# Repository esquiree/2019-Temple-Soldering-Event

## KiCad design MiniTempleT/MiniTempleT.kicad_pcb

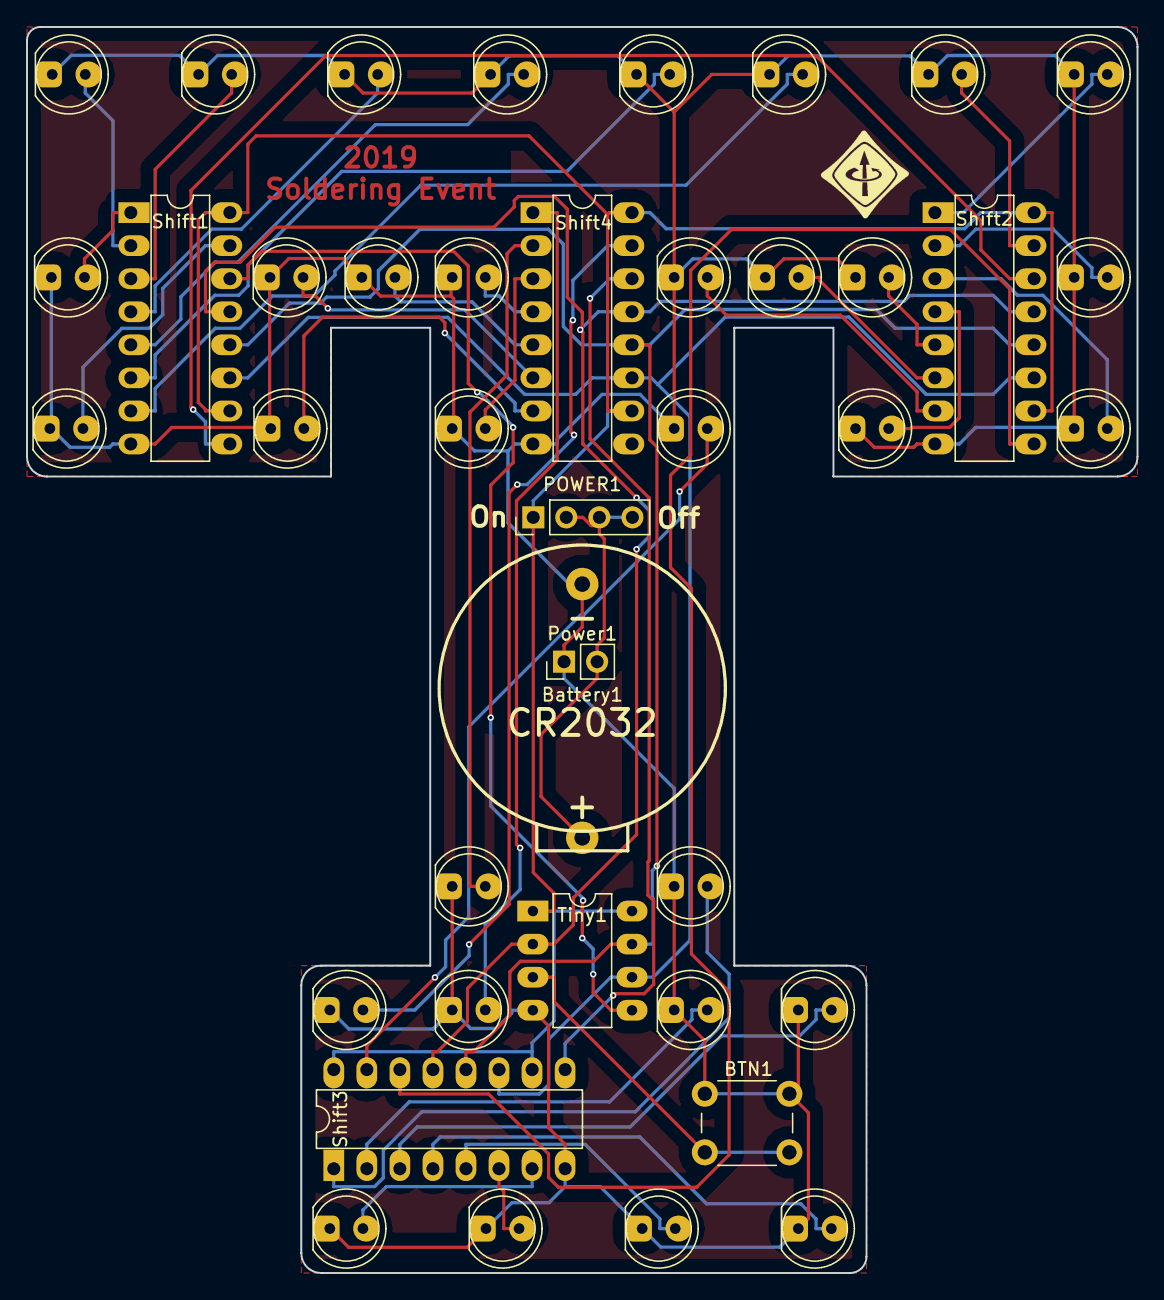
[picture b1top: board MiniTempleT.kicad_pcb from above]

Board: 2 copper layers, 85.3 x 95.8 mm, 43 parts (0 on the bottom side), 43 nets.

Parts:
BTN1: Conn_01x02; SW_PUSH_6mm_h5mm
Battery1: Conn_01x02; CR2032 Housing
D1, D2, D3, D4, D5, D6, D7, D8, D9, D10, D11, D12, D13, D14, D15, D16, D17, D18, D19, D20, D21, D22, D23, D24, D25, D26, D27, D28, D29, D30, D31, D32: LED; LED_D5.0mm_BigPads
G1: LOGO; TEMPLE IEEE 7mm SOLDER NEG
G2: LOGO1; IEEE LOGO 7mm SILK NEG
POWER1: CONN_01X04; Pin_Header_Straight_1x04_Pitch2.54mm
Power1: Conn_01x02; Pin_Header_Straight_1x02_Pitch2.54mm
Shift1, Shift2, Shift3, Shift4: 74HC595; DIP16-EzSolder
Tiny1: ATTINY85-20PU; DIP-8_W7.62mm_LongPads

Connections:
GND: BTN1.1, Battery1.1, D1.1, D2.1, D3.1, D4.1, D5.1, D6.1, D7.1, D8.1, D9.1, D10.1, D11.1, D12.1, D13.1, D14.1, D15.1, D16.1, D17.1, D18.1, D19.1, D20.1, D21.1, D22.1, D23.1, D24.1, D25.1, D26.1, D27.1, D28.1, D29.1, D30.1, D31.1, D32.1, Power1.1, Shift1.8, Shift2.8, Shift3.8, Shift4.8, Tiny1.4
Master_Reset: POWER1.1, Shift1.10, Shift1.16, Shift2.10, Shift2.16, Shift3.10, Shift3.16, Shift4.10, Shift4.16, Tiny1.1, Tiny1.8
unnamed: BTN1.2, Tiny1.3
unnamed: Battery1.2, POWER1.2, POWER1.3, POWER1.4, Power1.2
unnamed: D1.2, Shift1.15
unnamed: D2.2, Shift1.1
unnamed: D3.2, Shift1.2
unnamed: D4.2, Shift1.3
unnamed: D5.2, Shift1.4
unnamed: D6.2, Shift1.5
unnamed: D7.2, Shift1.6
unnamed: D8.2, Shift1.7
unnamed: D9.2, Shift2.15
unnamed: D10.2, Shift2.1
unnamed: D11.2, Shift2.2
unnamed: D12.2, Shift2.3
unnamed: D13.2, Shift2.4
unnamed: D14.2, Shift2.5
unnamed: D15.2, Shift2.6
unnamed: D16.2, Shift2.7
unnamed: D17.2, Shift3.15
unnamed: D18.2, Shift3.1
unnamed: D19.2, Shift3.2
unnamed: D20.2, Shift3.3
unnamed: D21.2, Shift3.4
unnamed: D22.2, Shift3.5
unnamed: D23.2, Shift3.6
unnamed: D24.2, Shift3.7
unnamed: D25.2, Shift4.15
unnamed: D26.2, Shift4.1
unnamed: D27.2, Shift4.2
unnamed: D28.2, Shift4.3
unnamed: D29.2, Shift4.4
unnamed: D30.2, Shift4.5
unnamed: D31.2, Shift4.6
unnamed: D32.2, Shift4.7
unnamed: Shift2.9, Shift3.14
unnamed: Shift3.9, Shift4.14
Out1: Shift1.9, Shift2.14
Output_Enable: Shift1.13, Shift2.13, Shift3.13, Shift4.13, Tiny1.2
Reg_Clock: Shift1.12, Shift2.12, Shift3.12, Shift4.12, Tiny1.7
Serial_Clock: Shift1.11, Shift2.11, Shift3.11, Shift4.11, Tiny1.6
Serial_Data: Shift1.14, Tiny1.5

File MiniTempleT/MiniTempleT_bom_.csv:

Component,Description,Part,References,Value,Footprint,Quantity Per PCB,Datasheet
1,"Generic connector, single row, 01x02",Conn_01x02,BTN1,Conn_01x02,SW_PUSH_6mm_h5mm,1,
2,"Generic connector, single row, 01x02",Conn_01x02,Battery1,Conn_01x02,CR2032 Housing,1,
3,LED generic,LED,D1 D2 D3 D4 D5 D6 D7 D8 D9 D10 D11 D12 D13 D14 D15 D16 D17 D18 D19 D20 D21 D22 D23 D24 D25 D26 D27 D28 D29 D30 D31 D32 D33 D34 D35 D36 D37 D38,LED,LED_D5.0mm_BigPads,38,
4,"Generic connector, single row, 01x04",Conn_01x04,POWER1,CONN_01X04,Pin_Header_Straight_1x04_Pitch2.54mm,1,
5,"Generic connector, single row, 01x02",Conn_01x02,Power1,Conn_01x02,Pin_Header_Straight_1x02_Pitch2.54mm,1,
6,8-bit serial in/out Shift Register 3-State Outputs,74HC595,Shift1 Shift2 Shift3 Shift4 Shift5,74HC595,SOIC-16W_5.3x10.2mm_Pitch1.27mm,5,http://www.ti.com/lit/ds/symlink/sn74hc595.pdf
7,"ATTINY85, PDIP8, 8k Flash, 512B SRAM, 512B EEPROM, Debug Wire",ATTINY85-20PU,Tiny85,ATTINY85-20PU,DIP-8_W7.62mm,1,http://www.atmel.com/images/atmel-2586-avr-8-bit-microcontro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





Component Groups:,7
Component Count:,48
Fitted Components:,48
Number of PCBs:,1
Total components:,48
Schematic Version:,
Schematic Date:,
BoM Date:,1/25/2019 21:08:16
Schematic Source:,C:\Users\Reed\Documents\MiniTempleT\MiniTempleT.sch
KiCad Version:,Eeschema (5.0.0)

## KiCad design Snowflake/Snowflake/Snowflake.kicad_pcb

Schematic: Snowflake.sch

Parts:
Battery1: Conn_01x02; CR2032 Housing
Button1: SW_Push; SW_PUSH_6mm_h5mm
D1, D2, D3, D4, D5, D6, D7, D8, D9, D10, D11, D12, D13, D14, D15, D16: LED; LED_D5.0mm_BigPads
Power1: Conn_01x04; Pin_Header_Straight_1x04_Pitch2.54mm
Shift1: 74HC595; DIP16-EzSolder
Tiny85: ATtiny85-20PU; DIP-8_W7.62mm_LongPads

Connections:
BTN: Button1.1, Tiny85.3 (XTAL2/PB4)
GND: Battery1.1, Button1.2, D1.1, D2.1, D3.1, D4.1, D5.1, D6.1, D7.1, D8.1, D9.1, D10.1, D11.1, D12.1, D13.1, D14.1, D15.1, D16.1, Shift1.8, Tiny85.4 (GND)
unnamed: Battery1.2, Power1.2, Power1.3, Power1.4
unnamed: D1.2, D2.2, Shift1.15
unnamed: D3.2, D4.2, Shift1.1
unnamed: D5.2, D6.2, Shift1.2
unnamed: D7.2, D8.2, Shift1.3
unnamed: D9.2, D10.2, Shift1.4
unnamed: D11.2, D12.2, Shift1.5
unnamed: D13.2, D14.2, Shift1.6
unnamed: D15.2, D16.2, Shift1.7
unnamed: Shift1.11, Tiny85.6 (PB1)
unnamed: Shift1.12, Tiny85.7 (PB2)
unnamed: Shift1.13, Tiny85.2 (XTAL1/PB3)
unnamed: Shift1.14, Tiny85.5 (AREF/PB0)
VCC: Power1.1, Shift1.10, Shift1.16, Tiny85.1 (~RESET~/PB5), Tiny85.8 (VCC)

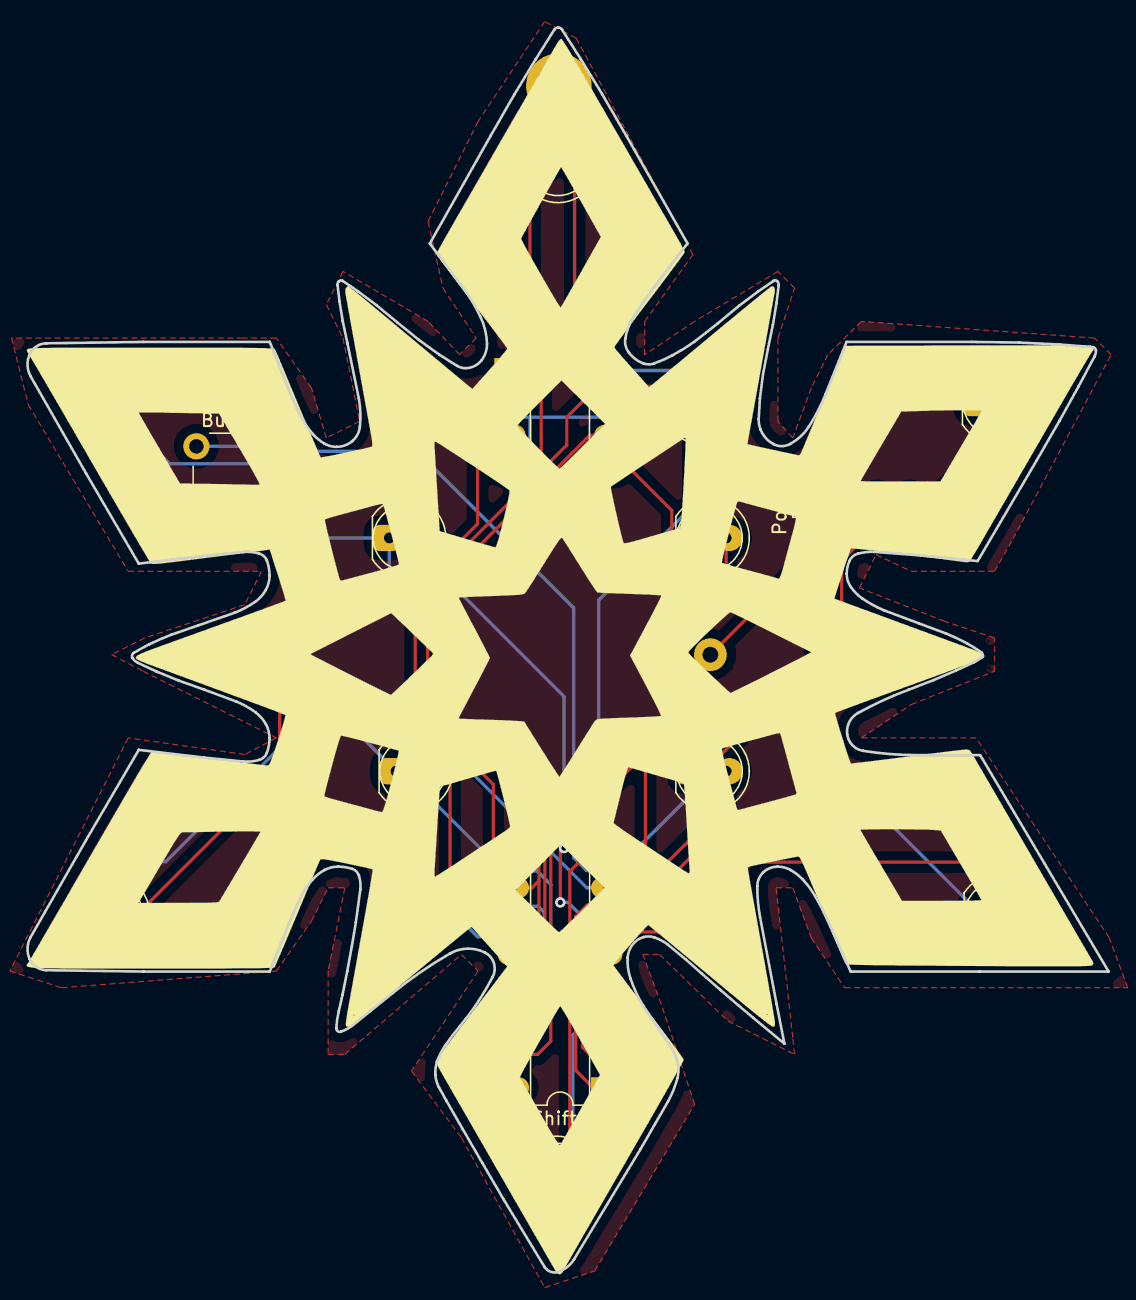
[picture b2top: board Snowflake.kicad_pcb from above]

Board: 2 copper layers, 82.4 x 94.9 mm, 22 parts (1 on the bottom side), 16 nets.

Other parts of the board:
g1: 4mm Mount

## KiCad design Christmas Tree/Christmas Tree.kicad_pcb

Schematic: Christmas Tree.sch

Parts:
BTN1: SW_SPST; SW_PUSH_6mm_h5mm
Battery1: Bat; CR2032 Housing
D1, D2, D3, D4, D5, D6, D7, D8, D9, D10, D11, D12, D13, D14, D15, D16, D17, D18, D19, D20, D21, D22, D23: LED; LED_D5.0mm_BigPads
Power1: Conn_01x04; Pin_Header_Straight_1x04_Pitch2.54mm
Shift1: 74HC595; DIP16-EzSolder
Tiny85: ATtiny85-20PU; DIP-8_W7.62mm_LongPads

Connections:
A: D22.2, D23.2, Shift1.15
B: D1.2, D2.2, D3.2, Shift1.1
C: D4.2, D5.2, D6.2, Shift1.2
D: D7.2, D8.2, D9.2, Shift1.3
E: D10.2, D11.2, D12.2, Shift1.4
F: D13.2, D14.2, D15.2, Shift1.5
G: D16.2, D17.2, D18.2, Shift1.6
GND: BTN1.2, Battery1.1, D1.1, D2.1, D3.1, D4.1, D5.1, D6.1, D7.1, D8.1, D9.1, D10.1, D11.1, D12.1, D13.1, D14.1, D15.1, D16.1, D17.1, D18.1, D19.1, D20.1, D21.1, D22.1, D23.1, Shift1.8, Tiny85.4 (GND)
H: D19.2, D20.2, D21.2, Shift1.7
Master_Reset: Power1.2, Power1.3, Power1.4, Shift1.10, Shift1.16, Tiny85.1 (~RESET~/PB5), Tiny85.8 (VCC)
unnamed: BTN1.1, Tiny85.3 (XTAL2/PB4)
unnamed: Battery1.2, Power1.1
Output_Enable: Shift1.13, Tiny85.2 (XTAL1/PB3)
Reg_Clock: Shift1.12, Tiny85.7 (PB2)
Serial_Clock: Shift1.11, Tiny85.6 (PB1)
Serial_Data: Shift1.14, Tiny85.5 (AREF/PB0)

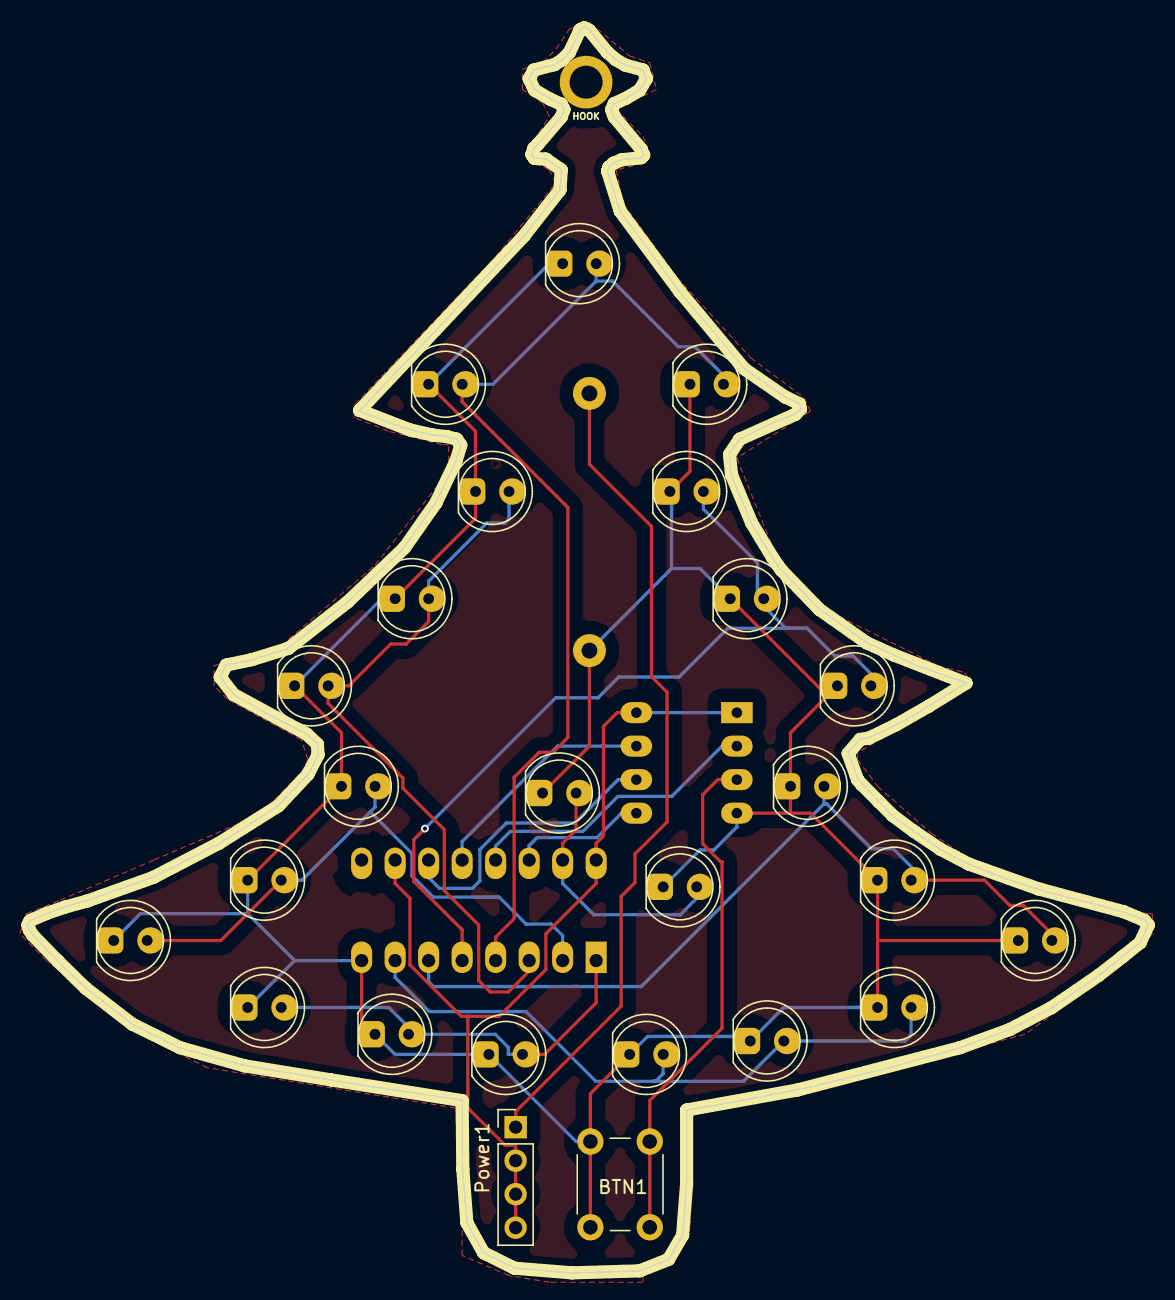
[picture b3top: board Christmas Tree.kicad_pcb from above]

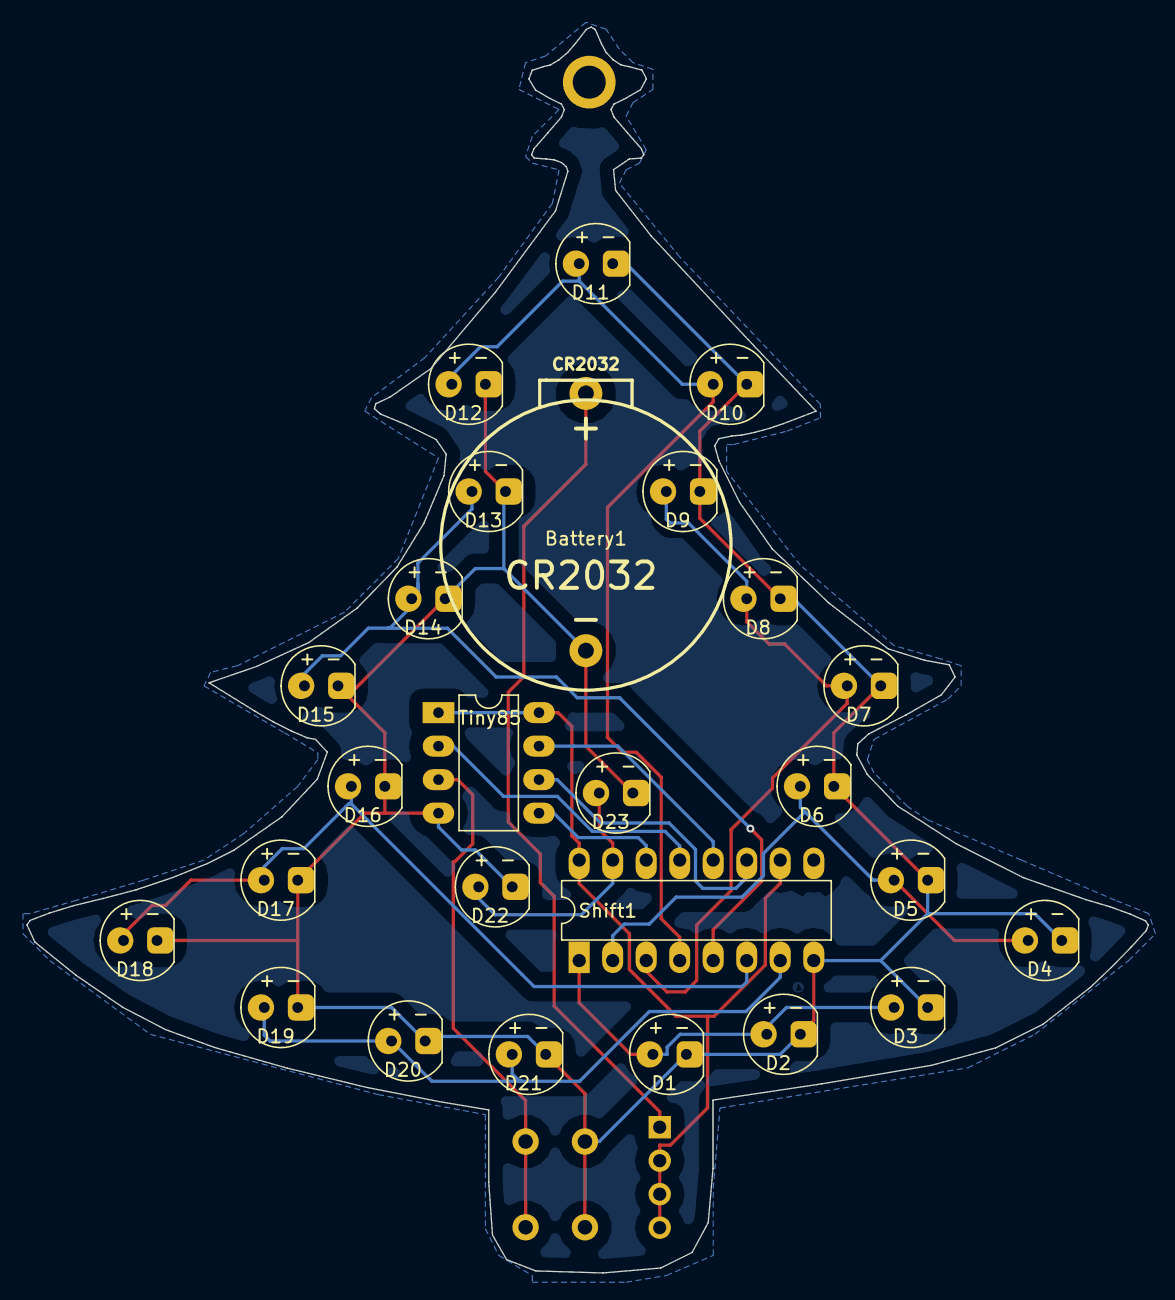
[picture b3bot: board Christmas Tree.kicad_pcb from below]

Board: 2 copper layers, 85.0 x 94.4 mm, 29 parts (3 on the bottom side), 16 nets.

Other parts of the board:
HOOK: 4mm Mount

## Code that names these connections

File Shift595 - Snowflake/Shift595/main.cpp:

#include <avr/io.h>
#define F_CPU 1000000UL
#include <util/delay.h>
#include <avr/interrupt.h>
#include <avr/eeprom.h>

/***************************************

Snow Flake AVR code for Attiny85

****************************************/

#define HC595_PORT   PORTB
#define HC595_DDR    DDRB

#define HC595_DS_POS PB0      //Data pin (DS) pin location

#define HC595_SH_CP_POS PB1      //Shift Clock (SH_CP) pin location 
#define HC595_ST_CP_POS PB2      //Store Clock (ST_CP) pin location
#define HC595_OE_POS PB3




uint8_t mode = 0;
uint8_t j = 0;
uint8_t coolDown = 0;


void HC595Init()
{
   //Make the Data(DS), Shift clock (SH_CP), Store Clock (ST_CP) lines output
   HC595_DDR|=((1<<HC595_SH_CP_POS)|(1<<HC595_ST_CP_POS)|(1<<HC595_DS_POS)|(1<<HC595_OE_POS));
   HC595_PORT&=(~(1<<HC595_OE_POS));//LOW
}


//Low level macros to change data (DS)lines
#define HC595DataHigh() (HC595_PORT|=(1<<HC595_DS_POS))

#define HC595DataLow() (HC595_PORT&=(~(1<<HC595_DS_POS)))

//Sends a clock pulse on SH_CP line
void HC595Pulse()
{
   //Pulse the Shift Clock

   HC595_PORT|=(1<<HC595_SH_CP_POS);//HIGH

   HC595_PORT&=(~(1<<HC595_SH_CP_POS));//LOW

}


void HC595Latch()
{

   HC595_PORT|=(1<<HC595_ST_CP_POS);//HIGH
   _delay_us(1);

   HC595_PORT&=(~(1<<HC595_ST_CP_POS));//LOW
   _delay_us(1);
}


void HC595Write(uint8_t data)
{
   for(uint8_t i=0;i<8;i++)
   {

      if(data & 0b10000000)
      {
         HC595DataHigh();
      }
      else
      {
         HC595DataLow();
      }
      HC595Pulse();  //Pulse the Clock line
      data=data<<1;  //Now bring next bit at MSB position

   }

   //HC595Latch();
}






void Wait()
{
	_delay_ms(500);
}

void writeByte(uint8_t byte0)
{

	HC595Write(byte0);
	HC595Latch();
}

void EEPROM_write(uint8_t uiAddress, uint8_t ucData) //Stolen from https://stackoverflow.com/questions/4412111/avr-eeprom-read-write
{
	while(EECR & (1<<EEPE));    /* Wait for completion of previous write */
	EEARH = 0x00;
	EEARL = uiAddress;
	EEDR = ucData;
	cli();
	EECR |= (1<<EEMPE);     /* Write logical one to EEMPE */
	EECR |= (1<<EEPE);      /* Start eeprom write by setting EEPE */
	sei();
}
unsigned char EEPROM_read(uint8_t uiAddress) //Stolen from https://stackoverflow.com/questions/4412111/avr-eeprom-read-write
{
	while(EECR & (1<<EEPE)); /* Wait for completion of previous write */

	EEARH = (uiAddress>>8);  /* Set up address register */
	EEARL = uiAddress;

	EECR |= (1<<EERE);       /* Start eeprom read by writing EERE */

	return EEDR;             /* Return data from Data Register */
}



ISR(PCINT0_vect)
{
	if (((PINB&(1<<PB4)) == 0x00) && (coolDown == 0x00))
	{
		mode++;
		j = 0xFD; //Exit current mode loop
		//coolDown = 0x0F;
		if (mode >= 7){ //Max mode options - 1
			mode = 0;
		}
		//Set up Timer1 for btn cool down 
		coolDown = 1;
		TCCR0B = (2 << CS00);              //div8
		OCR0B = F_CPU/8 * 0.000500 - 1;    // 500us compare value
		TIMSK |= (1<<OCIE0B);              //if you want interrupt				
	}
}

ISR(TIMER0_COMPB_vect)
{
	//Cool Down timer complete
	coolDown = 0x00;
	TIMSK = 0x00;  //Stop the counter
	EEPROM_write(0x07, mode); // Save mode for next power up
}

int main()
{
	HC595Init();
	PORTB ^= (1<<PB4); //Btn 
	uint8_t pattern1[] = {0x01,0x03,0x07,0x0F,0x1F,0x3F,0xBF,0xFF,0x7F,0xBF,0x3F,0x3E,0x3C,0x38,0x30,0x20};  
	uint8_t pattern2[] = {0x01,0x05,0x15,0x17,0x1F,0x3F,0xFF};
	uint8_t pattern3[] = {0xFF, 0x3F};
	uint8_t pattern4[] = {0xFE,0xFD,0xFB,0xF7,0xEF,0xDF,0xFF};
	uint8_t pattern5[] = {0xFF, 0xC0};
	mode = EEPROM_read(0x07); // Read mode selection from last power cycle
	if(mode > 0x07){ //catch any errors in EEPROM
		mode = 0x00;
	}
	
	
	GIMSK |= (1<<PCIE);		
	PCMSK |= (1<<PB4);
	sei();
	
	
		
	while(1)
	{		
		if (mode == 0)
		{
			for (j=0;j<2;j++)
			{
				writeByte(pattern3[j]);
				Wait();	
				Wait();
			}
		}
		if (mode == 1)
		{
			for (j=0;j<16;j++)
			{
				writeByte(pattern1[j]);
				Wait();
			}
		}
		if (mode == 2)
		{
			for (j=0;j<7;j++)
			{
				writeByte(pattern2[j]);
				Wait();
			}
			
			for (j=8;j>0;j--)
			{
				if (mode == 2) //Check for exit condition
				{
					writeByte(pattern2[j]);
					Wait();
				}
			}
					
		}
		if (mode == 3)
		{
			for (j=0;j<6;j++)
			{
				writeByte(pattern4[j]);
				Wait();
			}
			
		}
		if (mode == 4)
		{
			for (j=0;j<2;j++)
			{
				writeByte(pattern5[j]);
				Wait();
				Wait();
			}
		}
		if (mode == 5)
		{
			uint8_t shiftedNum =0x00;
			for (j=0;j<9;j++)
			{
				writeByte(shiftedNum);
				shiftedNum = shiftedNum<<1;
				shiftedNum = shiftedNum + 1;				   
				Wait();										
			}		
		}
		if (mode == 6)
		{
			writeByte(0xFF);
			Wait();
		}		 	 
	}
}
